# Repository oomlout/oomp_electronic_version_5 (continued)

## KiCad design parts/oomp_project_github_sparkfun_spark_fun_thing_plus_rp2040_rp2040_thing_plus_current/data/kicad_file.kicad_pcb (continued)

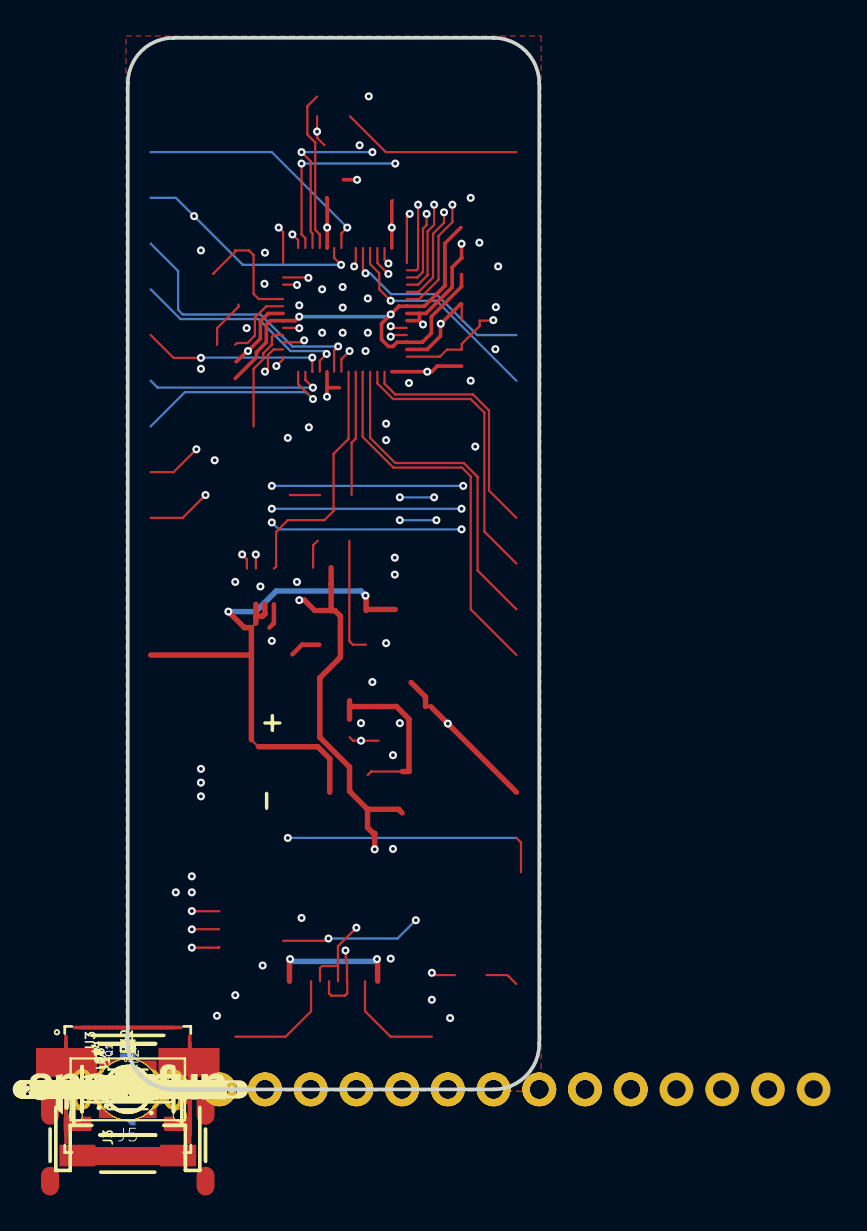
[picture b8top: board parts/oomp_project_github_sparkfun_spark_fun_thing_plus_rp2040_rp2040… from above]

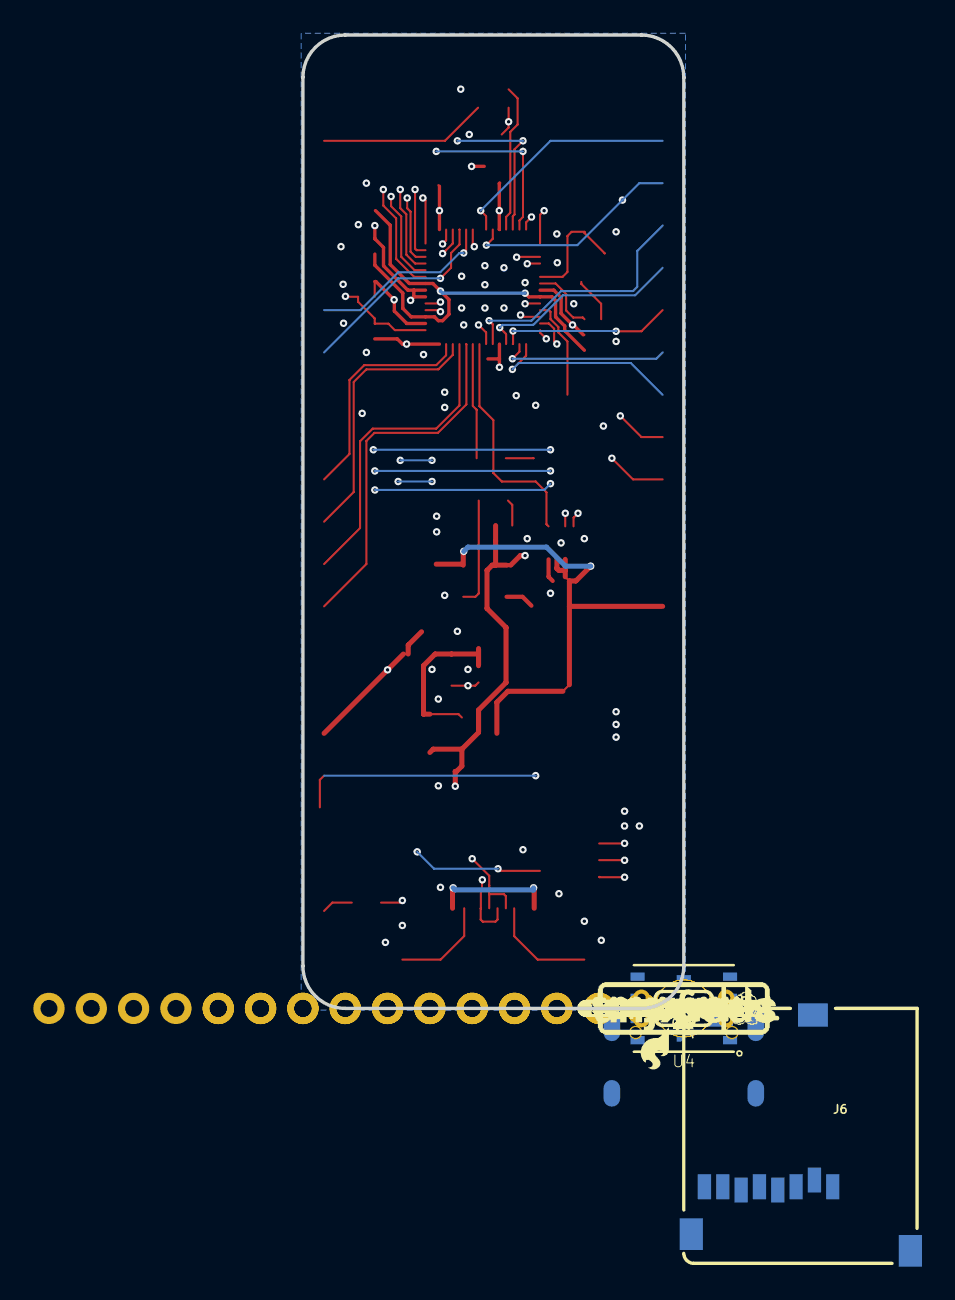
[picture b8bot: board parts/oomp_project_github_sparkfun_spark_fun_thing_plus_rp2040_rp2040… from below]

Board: 4 copper layers, 22.9 x 58.4 mm, 134 parts (42 on the bottom side), 62 nets.

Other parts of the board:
U$1: #_16#0
U$2: #_17#0
U$3: #_18#0
U$4: #_19#0
U$5: #_20#0
U$6: #_21#0
U$7: #_22#0
U$8: #_SCL#7#23#0
U$9: #_SDA#6#0
U$10: #WS2812_#0
U$11: #0#TX_#0
U$12: #1#RX_#0
U$13: #4#CIPO_#0
U$14: #3#COPI_#0
U$15: #2#SCK_#0
U$16: PWR0
U$17: #I�C#0
U$18: #29#ADC3_#0
U$19: #28#ADC2_#0
U$20: #27#ADC1_#0
U$21: #26#ADC0_#0
U$22: #_VUSB#0
U$23: #_EN#0
U$24: #_VBATT#0
U$25: #GND_#0
U$26: #AREF_#0
U$27: #3#3V_#0
U$28: ##RESET##0
U$29: RP2040_10
U$30: RP2040_20
U$31: ORDERING_INSTRUCTIONS
U$32: SFE_LOGO_NAME_FLAME_.1
U$33: #SCL_#0
U$34: #SDA_#0
U$35: #_#RESET##0
U$36: #_3#3V#0
U$37: #_AREF#0
U$38: #_GND#0
U$39: #_26#ADC0#0
U$40: #_27#ADC1#0
U$41: #_28#ADC2#0
U$42: #_29#ADC3#0
U$44: THING_PLUS0
U$45: SFE_LOGO_NAME_.1
U$47: THING_PLUS_0
U$54: 250
U$55: CHARGE0
U$56: BOOT0
U$57: #22_#0
U$58: #21_#0
U$59: #20_#0
U$60: #WS2812#0
U$61: #19_#0
U$62: #18_#0
U$63: #17_#0
U$64: QWIIC_4MM
U$65: #16_#0
U$66: #VUSB_#0
U$67: #EN_#0
U$68: #VBATT_#0
U$69, U$70: #_NC#0

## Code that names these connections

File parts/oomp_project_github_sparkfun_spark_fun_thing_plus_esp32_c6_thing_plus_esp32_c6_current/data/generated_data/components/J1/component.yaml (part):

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        pin_number: '7'
        pin_name: SCL
    - number: '3'
      name: GPIO6
      electrical_type: bidirectional
      graphic_style: line
      local_position:
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        pin_number: '23'
        pin_name: IO15
    - number: '4'
      name: GPIO5
      electrical_type: bidirectional
      graphic_style: line
      local_position:
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        pin_number: '21'
        pin_name: SDIO_D3/IO23
    - number: '5'
      name: GPIO4
      electrical_type: bidirectional
      graphic_style: line
      local_position:
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        pin_number: '10'
        pin_name: IO8
    - number: '6'
      name: GPIO3
      electrical_type: bidirectional
      graphic_style: line
      local_position:
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        pin_number: '11'
        pin_name: IO10
    - number: '7'
      name: GPIO2
      electrical_type: bidirectional
      graphic_style: line
      local_position:
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        pin_number: '12'
        pin_name: IO11
    - number: '8'
      name: GPIO1
      electrical_type: bidirectional
      graphic_style: line
      local_position:
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        pin_number: '20'
        pin_name: SDIO_D2/IO22
    - number: '9'
      name: GPIO0
      electrical_type: bidirectional
      graphic_style: line
      local_position:
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        pin_name: DAT3/~{CS}
      - reference: U1
        pin_number: '16'
        pin_name: SDIO_CMD/IO18
    - number: '10'
      name: V_USB
      electrical_type: bidirectional
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      connected_to:
      - reference: '#SUPPLY3'
        pin_number: '1'
        pin_name: V_USB
      - reference: '#SUPPLY8'
        pin_number: '1'
        pin_name: V_USB
      - reference: '#SUPPLY9'
        pin_number: '1'
        pin_name: V_USB
      - reference: '#SUPPLY11'
        pin_number: '1'
        pin_name: V_USB
      - reference: C3
        pin_number: '1'
        pin_name: '1'
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      connected_to:
      - reference: '#SUPPLY5'
        pin_number: '1'
        pin_name: V_BATT
      - reference: '#SUPPLY7'
        pin_number: '1'
        pin_name: V_BATT
      - reference: '#SUPPLY10'
        pin_number: '1'
        pin_name: V_BATT
      - reference: '#SUPPLY17'
        pin_number: '1'
        pin_name: V_BATT
      - reference: '#SUPPLY18'
        pin_number: '1'
        pin_name: V_BATT
      - reference: C4
        pin_number: '1'
        pin_name: '1'
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        pin_name: CLK/SCK
      - reference: U1
        pin_number: '17'
        pin_name: SDIO_CLK/IO19
    - number: '19'
      name: A5
      electrical_type: bidirectional
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    pin_name: 3.3V
  - reference: '#SUPPLY3'
    pin_number: '1'
    pin_name: V_USB
  - reference: '#SUPPLY4'
    pin_number: '1'
    pin_name: 3.3V
  - reference: '#SUPPLY5'
    pin_number: '1'
    pin_name: V_BATT
  - reference: '#SUPPLY6'
    pin_number: '1'
    pin_name: 3.3V
  - reference: '#SUPPLY7'
    pin_number: '1'
    pin_name: V_BATT
  - reference: '#SUPPLY8'
    pin_number: '1'
    pin_name: V_USB
  - reference: '#SUPPLY9'
    pin_number: '1'
    pin_name: V_USB
  - reference: '#SUPPLY10'
    pin_number: '1'
    pin_name: V_BATT
  - reference: '#SUPPLY11'
    pin_number: '1'
    pin_name: V_USB
  - reference: '#SUPPLY12'
    pin_number: '1'
    pin_name: 3.3V
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    pin_name: 3.3V
  - reference: '#SUPPLY17'
    pin_number: '1'
    pin_name: V_BATT
  - reference: '#SUPPLY18'
    pin_number: '1'
    pin_name: V_BATT
  - reference: '#SUPPLY19'
    pin_number: '1'
    pin_name: 3.3V
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    pin_name: IO9
  - reference: U1
    pin_number: '16'
    pin_name: SDIO_CMD/IO18
  - reference: U1
    pin_number: '17'
    pin_name: SDIO_CLK/IO19
  - reference: U1
    pin_number: '18'
    pin_name: SDIO_D0/IO20
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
